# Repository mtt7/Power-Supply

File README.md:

# Power Supply
Custom made power supply PCB board

## Folder structure

### Hardware
Contains KiCAD 5.1 files, schematics, pcb design, libraries.

### Production
Contains gerber files.

### Documentation
Contains datasheets, design guidelines.

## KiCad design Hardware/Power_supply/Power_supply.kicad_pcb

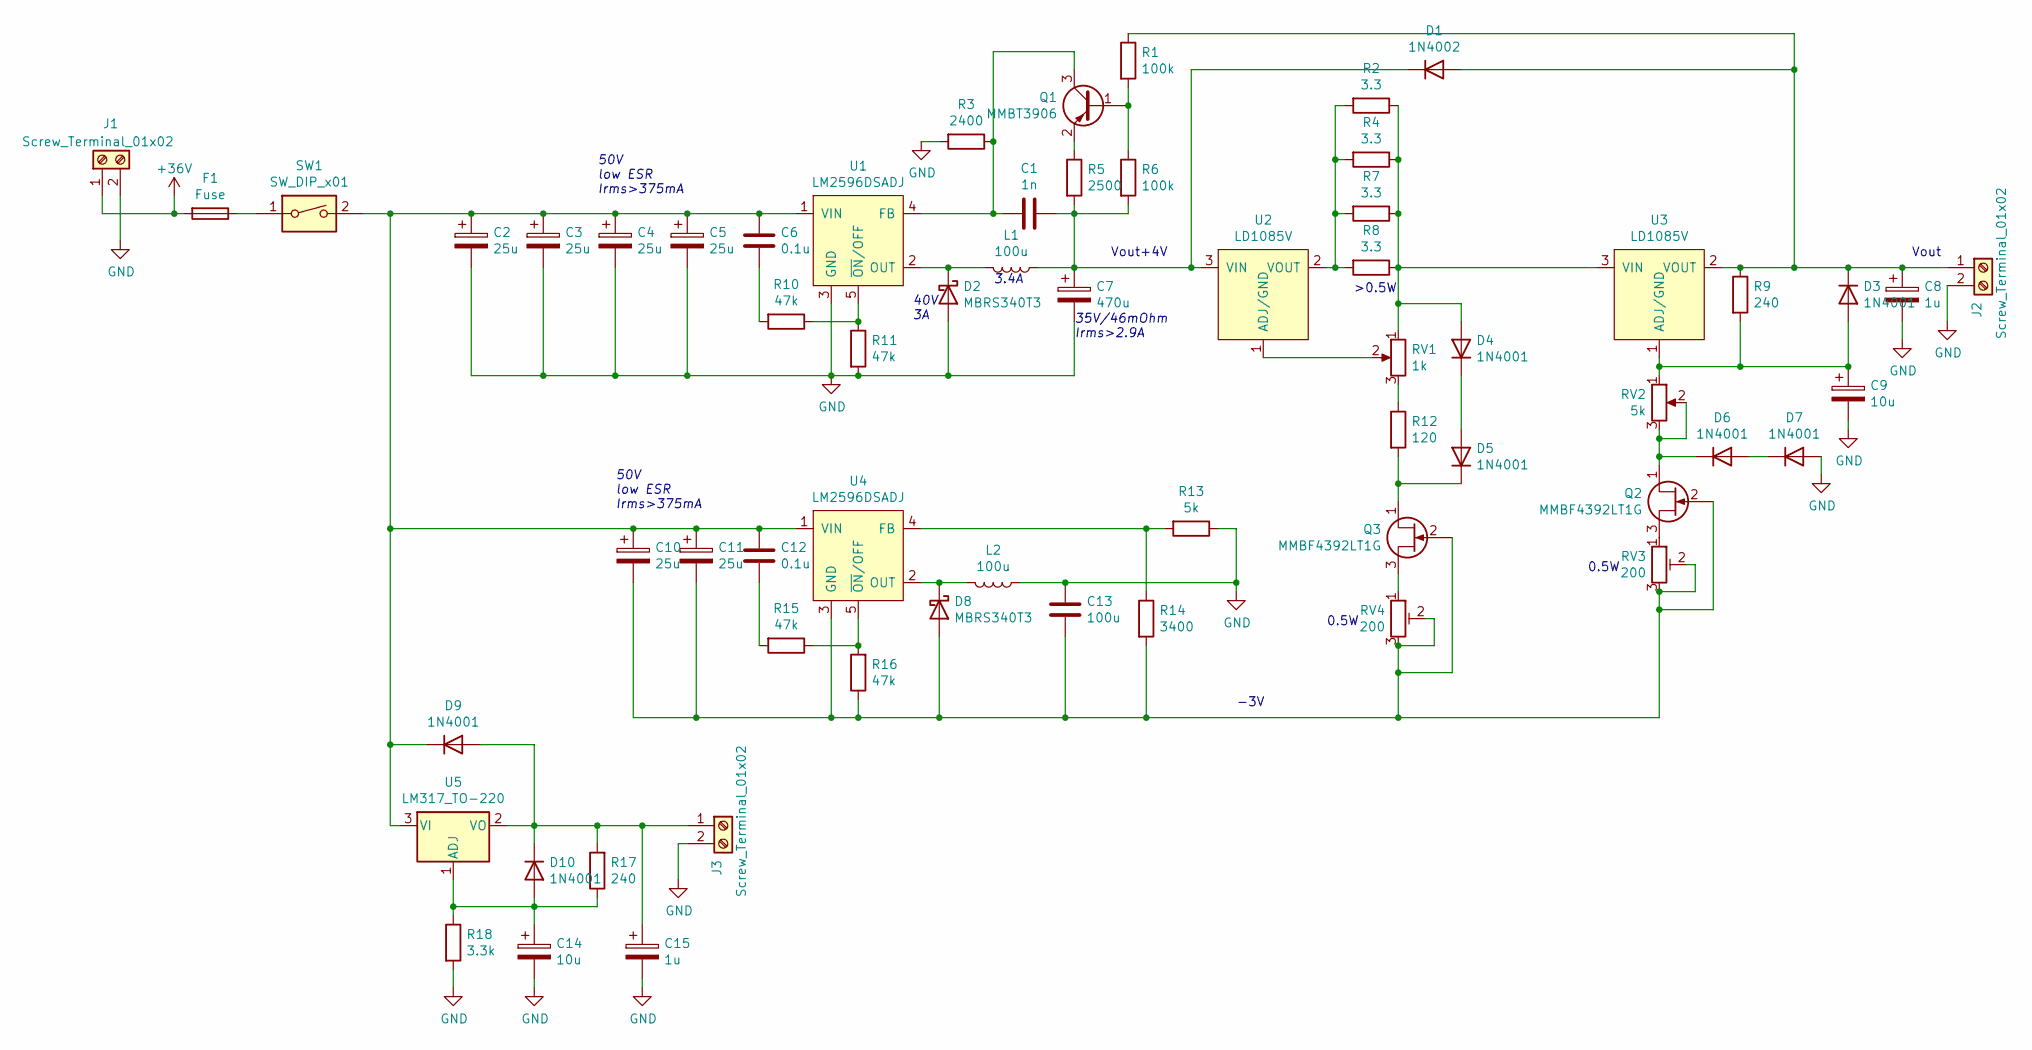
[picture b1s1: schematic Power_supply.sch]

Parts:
C1: 1n; C_1206_3216Metric_Pad1.42x1.75mm_HandSolder
C2, C3, C4, C5, C10, C11: 25u; CP_Radial_D5.0mm_P2.00mm
C6, C12: 0.1u; C_1206_3216Metric_Pad1.42x1.75mm_HandSolder
C7: 470u; CP_Radial_D10.0mm_P5.00mm
C8: 1u; C_1206_3216Metric_Pad1.42x1.75mm_HandSolder
C9: 10u; C_1206_3216Metric_Pad1.42x1.75mm_HandSolder
C13: 100u; CP_Radial_D8.0mm_P3.50mm
C14: 10u; CP_Radial_D5.0mm_P2.00mm
C15: 1u; CP_Radial_D4.0mm_P2.00mm
D1: 1N4002; D_5KP_P10.16mm_Horizontal
D2, D8: MBRS340T3; D_SMC2
D3, D4, D5, D6, D7, D9, D10: 1N4001; D_5KP_P10.16mm_Horizontal
F1: Fuse; Fuse_1206_3216Metric_Pad1.42x1.75mm_HandSolder
J1, J2, J3: Screw_Terminal_01x02; screw_terminal
L1, L2: 100u; L_Toroid_Vertical_L21.6mm_W9.1mm_P8.40mm_Bourns_5700
Q1: MMBT3906; SOT-23_Handsoldering
Q2, Q3: MMBF4392LT1G; SOT-23_Handsoldering
R1, R6: 100k; R_1206_3216Metric_Pad1.42x1.75mm_HandSolder
R2, R4, R7, R8: 3.3; R_2512_6332Metric_Pad1.52x3.35mm_HandSolder
R3: 2400; R_1206_3216Metric_Pad1.42x1.75mm_HandSolder
R5: 2500; R_1206_3216Metric_Pad1.42x1.75mm_HandSolder
R9: 240; R_1206_3216Metric_Pad1.42x1.75mm_HandSolder
R10, R11, R15, R16: 47k; R_1206_3216Metric_Pad1.42x1.75mm_HandSolder
R12: 120; R_1206_3216Metric_Pad1.42x1.75mm_HandSolder
R13: 5k; R_1206_3216Metric_Pad1.42x1.75mm_HandSolder
R14: 3400; R_1206_3216Metric_Pad1.42x1.75mm_HandSolder
R17: 240; R_Axial_DIN0207_L6.3mm_D2.5mm_P10.16mm_Horizontal
R18: 3.3k; R_Axial_DIN0207_L6.3mm_D2.5mm_P10.16mm_Horizontal
RV1: 1k; offboard_pot
RV2: 5k; offboard_pot
RV3, RV4: 200; trimmerTHT
SW1: SW_DIP_x01; offboard_switch
U1: LM2596DSADJ; TO-220-5_with_heatsink
U2, U3: LD1085V; TO-220-3_with_heatsink
U4: LM2596DSADJ; TO-220-5_P3.4x3.7mm_StaggerOdd_Lead3.8mm_Vertical
U5: LM317_TO-220; TO-220-3_Vertical

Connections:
+36V: F1.2, J1.1
GND: C2.2, C3.2, C4.2, C5.2, C7.2, C8.2, C9.2, C13.1, C14.2, C15.2, D2.2 (A), D7.2 (A), J1.2, J2.2, J3.2, L2.1, R3.2, R11.2, R13.1, R18.2, U1.3 (GND)
unnamed: C1.1, C7.1, D1.1 (K), L1.1, R5.2, R6.2, U2.3 (VIN)
unnamed: C1.2, Q1.3 (C), R3.1, U1.4 (FB)
unnamed: C6.2, R10.2
unnamed: C8.1, D1.2 (A), D3.1 (K), J2.1, R1.1, R9.1, U3.2 (VOUT)
unnamed: C9.1, D3.2 (A), R9.2, RV2.1, U3.1 (ADJ/GND)
unnamed: C2.1, C3.1, C4.1, C5.1, C6.1, C10.1, C11.1, C12.1, D9.1 (K), SW1.2, U1.1 (VIN), U4.1 (VIN), U5.3 (VI)
unnamed: C10.2, C11.2, C13.2, D8.2 (A), Q2.2 (G), Q3.2 (G), R14.2, R16.1, RV3.2, RV3.3, RV4.2, RV4.3, U4.3 (GND)
unnamed: C12.2, R15.2
unnamed: C14.1, D10.2 (A), R17.1, R18.1, U5.1 (ADJ)
unnamed: C15.1, D9.2 (A), D10.1 (K), J3.1, R17.2, U5.2 (VO)
unnamed: D2.1 (K), L1.2, U1.2 (OUT)
unnamed: D4.1 (K), D5.2 (A)
unnamed: D4.2 (A), R2.1, R4.1, R7.1, R8.1, RV1.1, U3.3 (VIN)
unnamed: D5.1 (K), Q3.1 (D), R12.2
unnamed: D6.1 (K), Q2.1 (D), RV2.2, RV2.3
unnamed: D6.2 (A), D7.1 (K)
unnamed: D8.1 (K), L2.2, U4.2 (OUT)
unnamed: F1.1, SW1.1
unnamed: Q1.1 (B), R1.2, R6.1
unnamed: Q1.2 (E), R5.1
unnamed: Q2.3 (S), RV3.1
unnamed: Q3.3 (S), RV4.1
unnamed: R2.2, R4.2, R7.2, R8.2, U2.2 (VOUT)
unnamed: R10.1, R11.1, U1.5 (~ON~/OFF)
unnamed: R12.1, RV1.3
unnamed: R13.2, R14.1, U4.4 (FB)
unnamed: R15.1, R16.2, U4.5 (~ON~/OFF)
unnamed: RV1.2, U2.1 (ADJ/GND)

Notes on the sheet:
3.4A
35V/46mOhm Irms>2.9A
40V 3A
>0.5W
0.5W
0.5W
-3V
Vout+4V
Vout
50V low ESR Irms>375mA

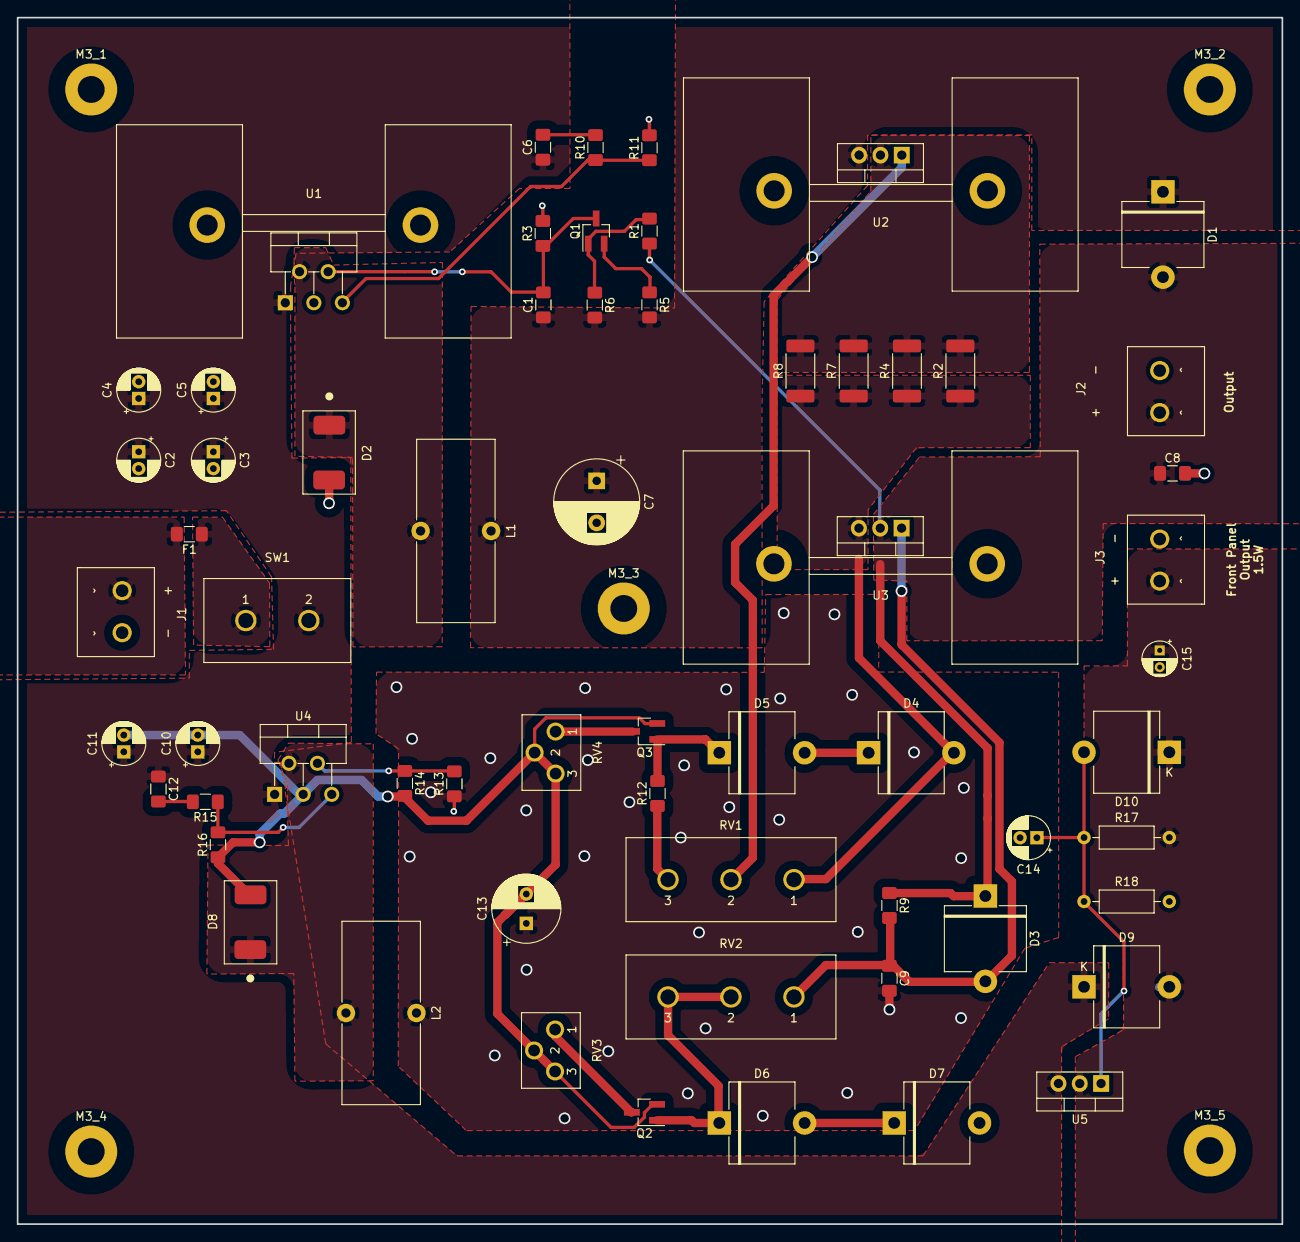
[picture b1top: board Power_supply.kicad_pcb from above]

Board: 2 copper layers, 150.6 x 143.7 mm, 67 parts (0 on the bottom side), 30 nets.

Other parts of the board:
M3_1, M3_2, M3_3, M3_4, M3_5: MountingHole_3.2mm_M3_Pad

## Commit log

2020-08-27 headlines update
